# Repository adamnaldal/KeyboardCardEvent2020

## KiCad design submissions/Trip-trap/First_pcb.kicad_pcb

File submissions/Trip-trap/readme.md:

# Trip-traps's Business card

A simple little macro pad, made by following ai03's guide: 

This is my first attempt at designing a pcb so it it is mostly a learning opportunity for me, therefore it doesn't do anything fancy.

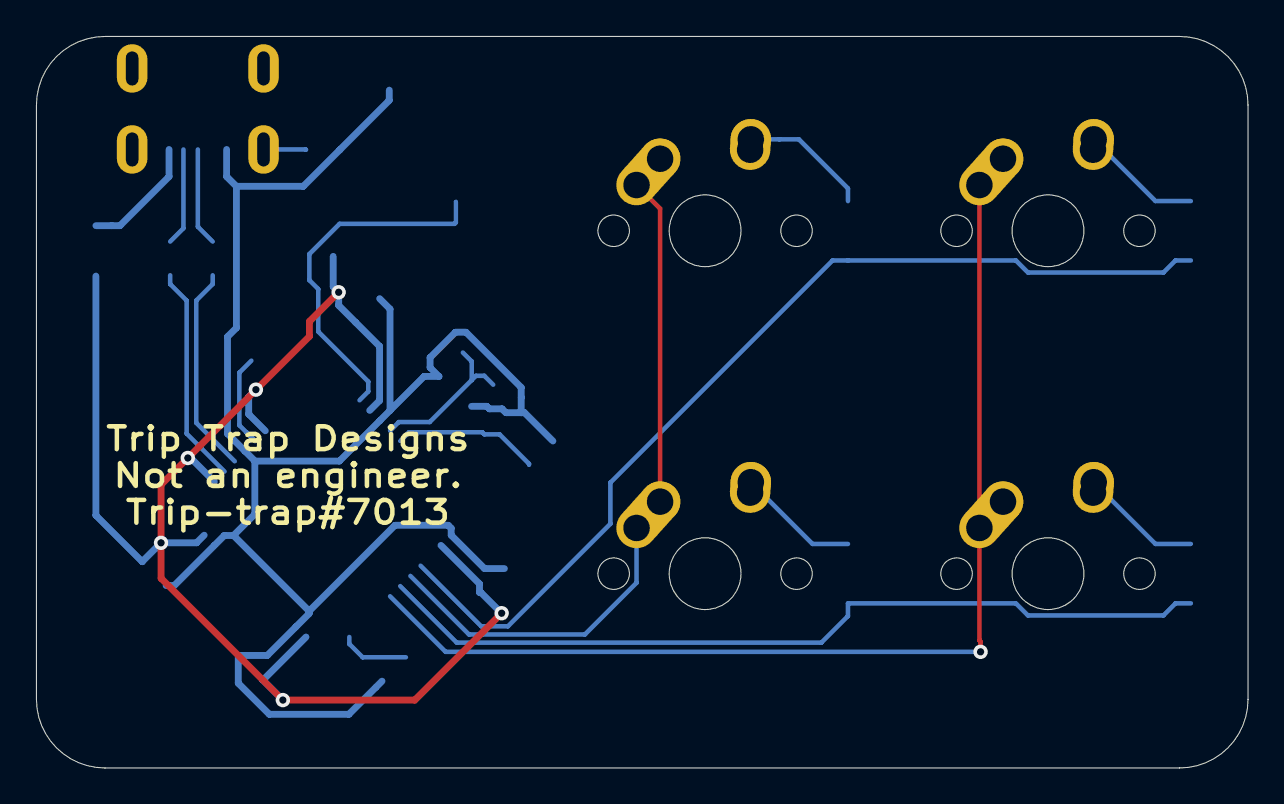
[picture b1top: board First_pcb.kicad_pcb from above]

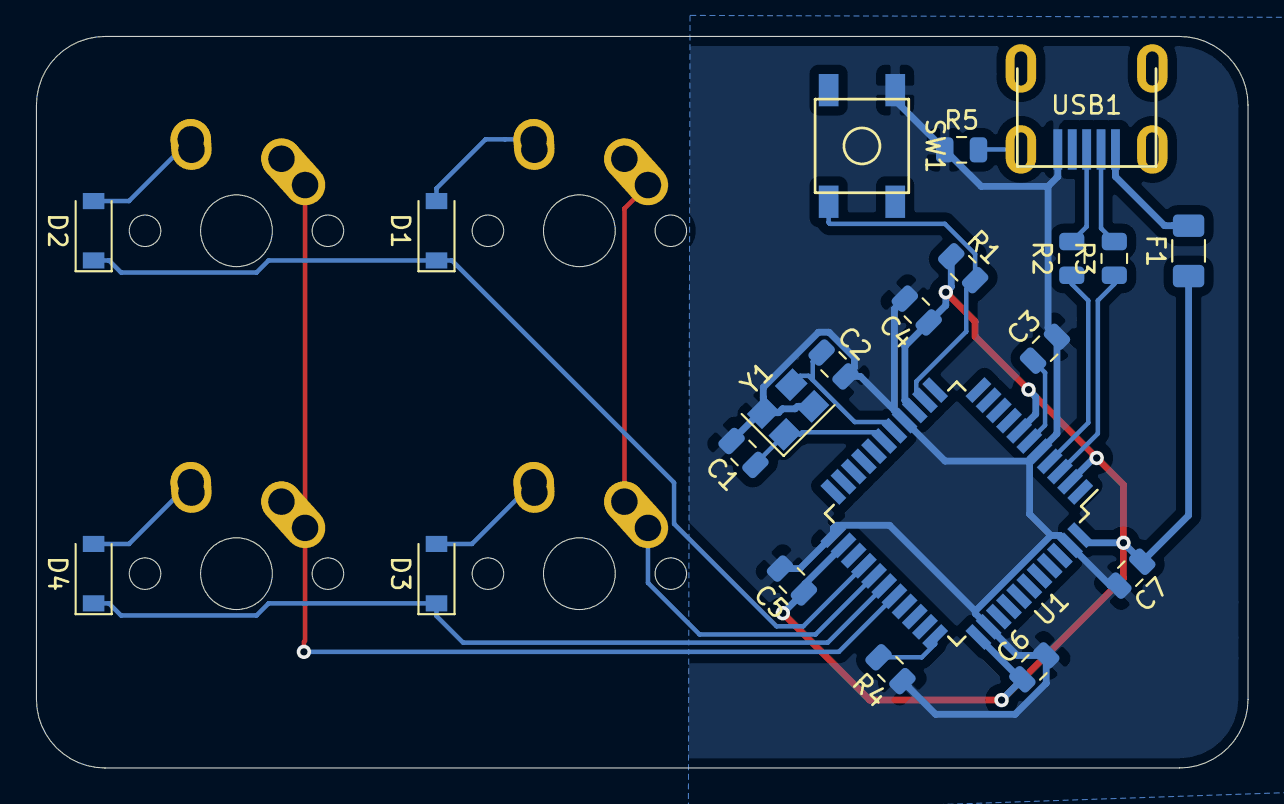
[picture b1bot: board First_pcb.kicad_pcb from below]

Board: 2 copper layers, 67.3 x 40.6 mm, 25 parts (21 on the bottom side), 21 nets.

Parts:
C1, C2: 22pF; C_0805_2012Metric
C3: 1uF; C_0805_2012Metric
C4, C5, C6: 0.1uF; C_0805_2012Metric
C7: 10uF; C_0805_2012Metric
D1, D2, D3, D4: D_Small; D_SOD-123
F1: 500mA; Fuse_1206_3216Metric
MX1, MX2, MX3, MX4: MX-NoLED; MX-1U-NoLED
R1, R4: 10k; R_0805_2012Metric
R2, R3: 22; R_0805_2012Metric
R5: 0; R_0805_2012Metric
SW1: SW_Push; SKQG-1155865
U1: ATmega32U4-AU; TQFP-44_10x10mm_P0.8mm
USB1: Molex-0548190589
Y1: 16MHz; Crystal_SMD_3225-4Pin_3.2x2.5mm

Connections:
+5V: C4.1, C5.1, C6.1, C7.1, F1.1, R1.1, U1.2, U1.7, U1.14, U1.24, U1.34, U1.44
Col0: MX1.1, MX3.1, U1.27
Col1: MX2.1, MX4.1, U1.29
D+: R2.2, USB1.3
D-: R3.2, USB1.4
GND: C1.2, C2.2, C3.2, C4.2, C5.2, C6.2, C7.2, R4.1, R5.1, SW1.1, U1.5, U1.15, U1.23, U1.35, U1.43, USB1.1, Y1.2, Y1.4
unnamed: C1.1, U1.17, Y1.1
unnamed: C2.1, U1.16, Y1.3
unnamed: C3.1, U1.6
unnamed: D1.2, MX1.2
unnamed: D2.2, MX2.2
unnamed: D3.2, MX3.2
unnamed: D4.2, MX4.2
unnamed: R1.2, SW1.2, U1.13
unnamed: R2.1, U1.4
unnamed: R3.1, U1.3
unnamed: R4.2, U1.33
unnamed: R5.2, USB1.6
Row0: D1.1, D2.1, U1.26
Row1: D3.1, D4.1, U1.28
VCC: F1.2, USB1.5

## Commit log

2020-04-09 added first finished pcb
2020-04-09 added license
2020-04-09 redid solder mask
